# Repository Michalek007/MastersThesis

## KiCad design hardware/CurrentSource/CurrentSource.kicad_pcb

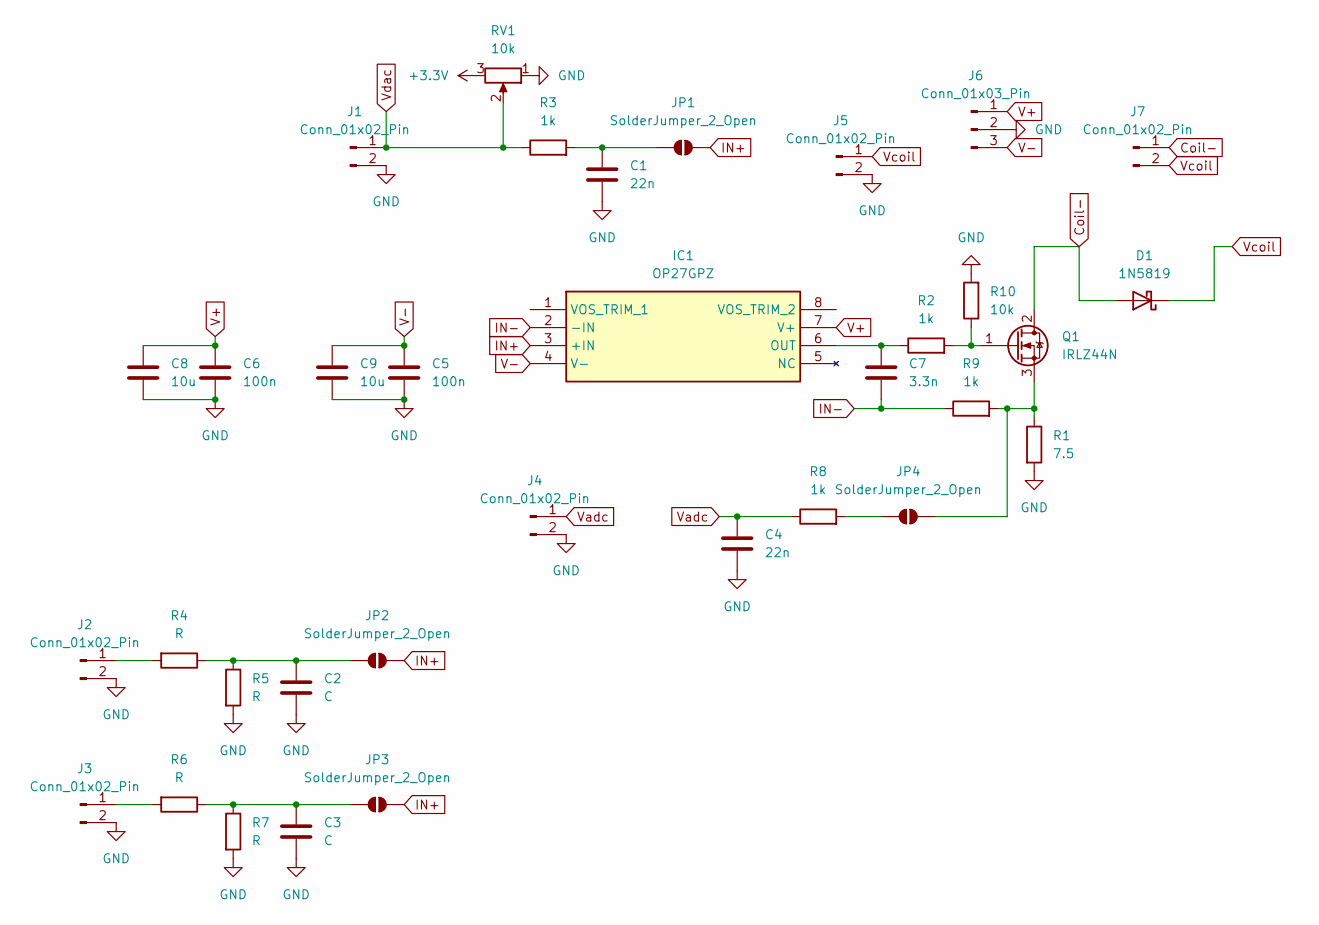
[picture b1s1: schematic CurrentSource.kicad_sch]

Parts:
C1, C4: 22n; C_0805_2012Metric
C2, C3: C; C_0805_2012Metric
C5, C6: 100n; C_0805_2012Metric
C7: 3.3n; C_0805_2012Metric
C8, C9: 10u; C_0805_2012Metric
D1: 1N5819; D_DO-41_SOD81_P10.16mm_Horizontal
IC1: OP27GPZ; DIP794W56P254L959H533Q8N; Mouser Part Number 584-OP27GPZ
J1, J2, J3, J4, J5, J7: Conn_01x02_Pin; PinHeader_1x02_P2.54mm_Vertical
J6: Conn_01x03_Pin; PinHeader_1x03_P2.54mm_Vertical
JP1, JP2, JP3, JP4: SolderJumper_2_Open; SolderJumper-2_P1.3mm_Open_Pad1.0x1.5mm
Q1: IRLZ44N; TO-220-3_Vertical
R1: 7.5; TO-220-2_Vertical
R2, R3, R8, R9: 1k; R_0805_2012Metric
R4, R5, R6, R7: R; R_0805_2012Metric
R10: 10k; R_0805_2012Metric
RV1: 10k; Potentiometer_ACP_CA6-H2,5_Horizontal

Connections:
+3.3V: RV1.3
Coil-: D1.2 (A), J7.1, Q1.2 (D)
GND: C1.2, C2.2, C3.2, C4.2, C5.2, C6.2, C8.2, C9.2, J1.2, J2.2, J3.2, J4.2, J5.2, J6.2, R1.2, R5.2, R7.2, R10.2, RV1.1
IN+: IC1.3 (+IN), JP1.2 (B), JP2.2 (B), JP3.2 (B)
IN-: C7.1, IC1.2 (-IN), R9.1
unnamed: C7.2, IC1.6 (OUT), R2.1
unnamed: J2.1, R4.2
unnamed: J3.1, R6.2
unnamed: C1.1, JP1.1 (A), R3.2
unnamed: C2.1, JP2.1 (A), R4.1, R5.1
unnamed: C3.1, JP3.1 (A), R6.1, R7.1
unnamed: JP4.1 (A), R8.2
unnamed: JP4.2 (B), Q1.3 (S), R1.1, R9.2
unnamed: Q1.1 (G), R2.2, R10.1
V+: C6.1, C8.1, IC1.7 (V+), J6.1
V-: C5.1, C9.1, IC1.4 (V-), J6.3
Vadc: C4.1, J4.1, R8.1
Vcoil: D1.1 (K), J5.1, J7.2
Vdac: J1.1, R3.1, RV1.2

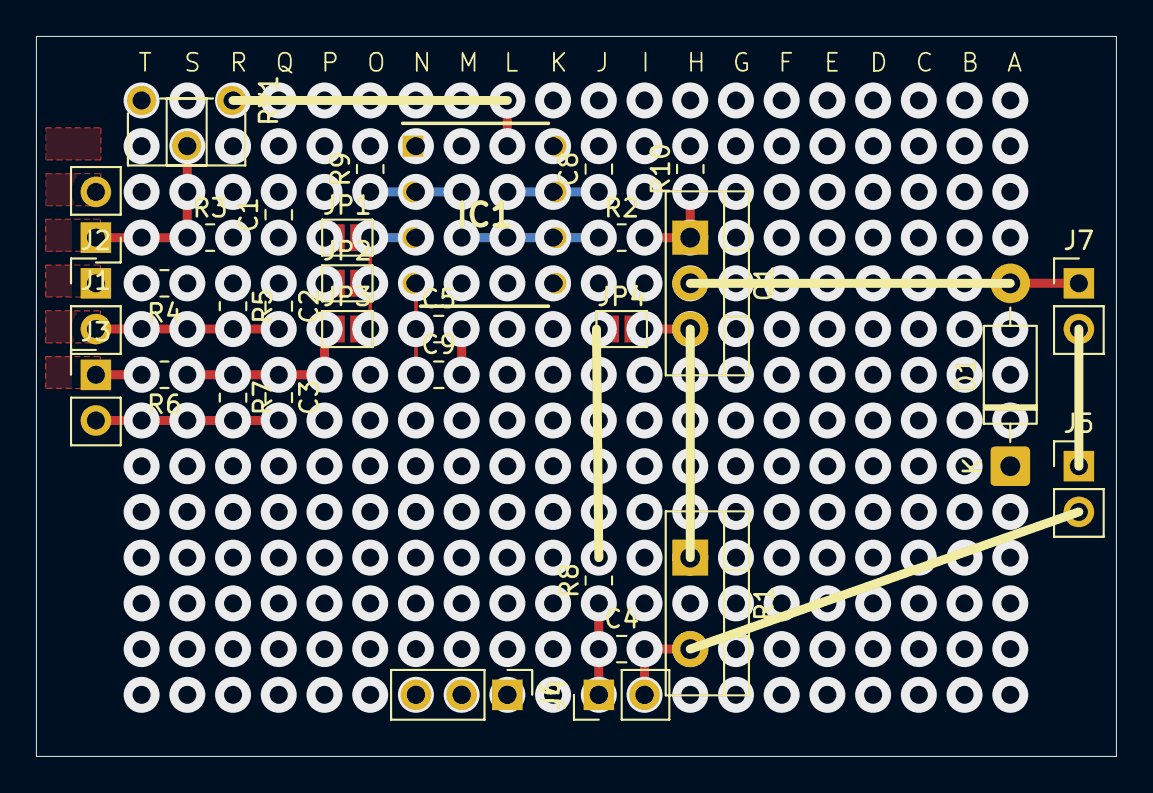
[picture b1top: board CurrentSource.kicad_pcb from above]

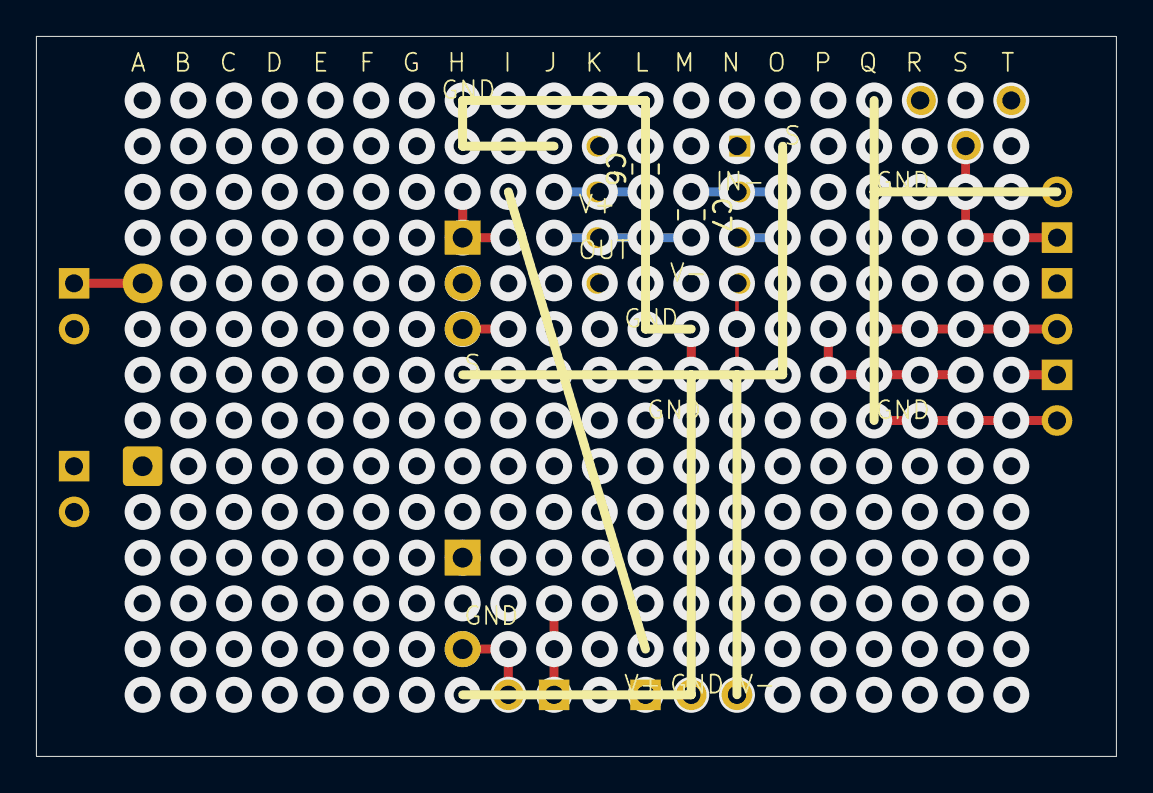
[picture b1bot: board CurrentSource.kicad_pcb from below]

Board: 2 copper layers, 60.0 x 40.0 mm, 34 parts (2 on the bottom side), 18 nets.

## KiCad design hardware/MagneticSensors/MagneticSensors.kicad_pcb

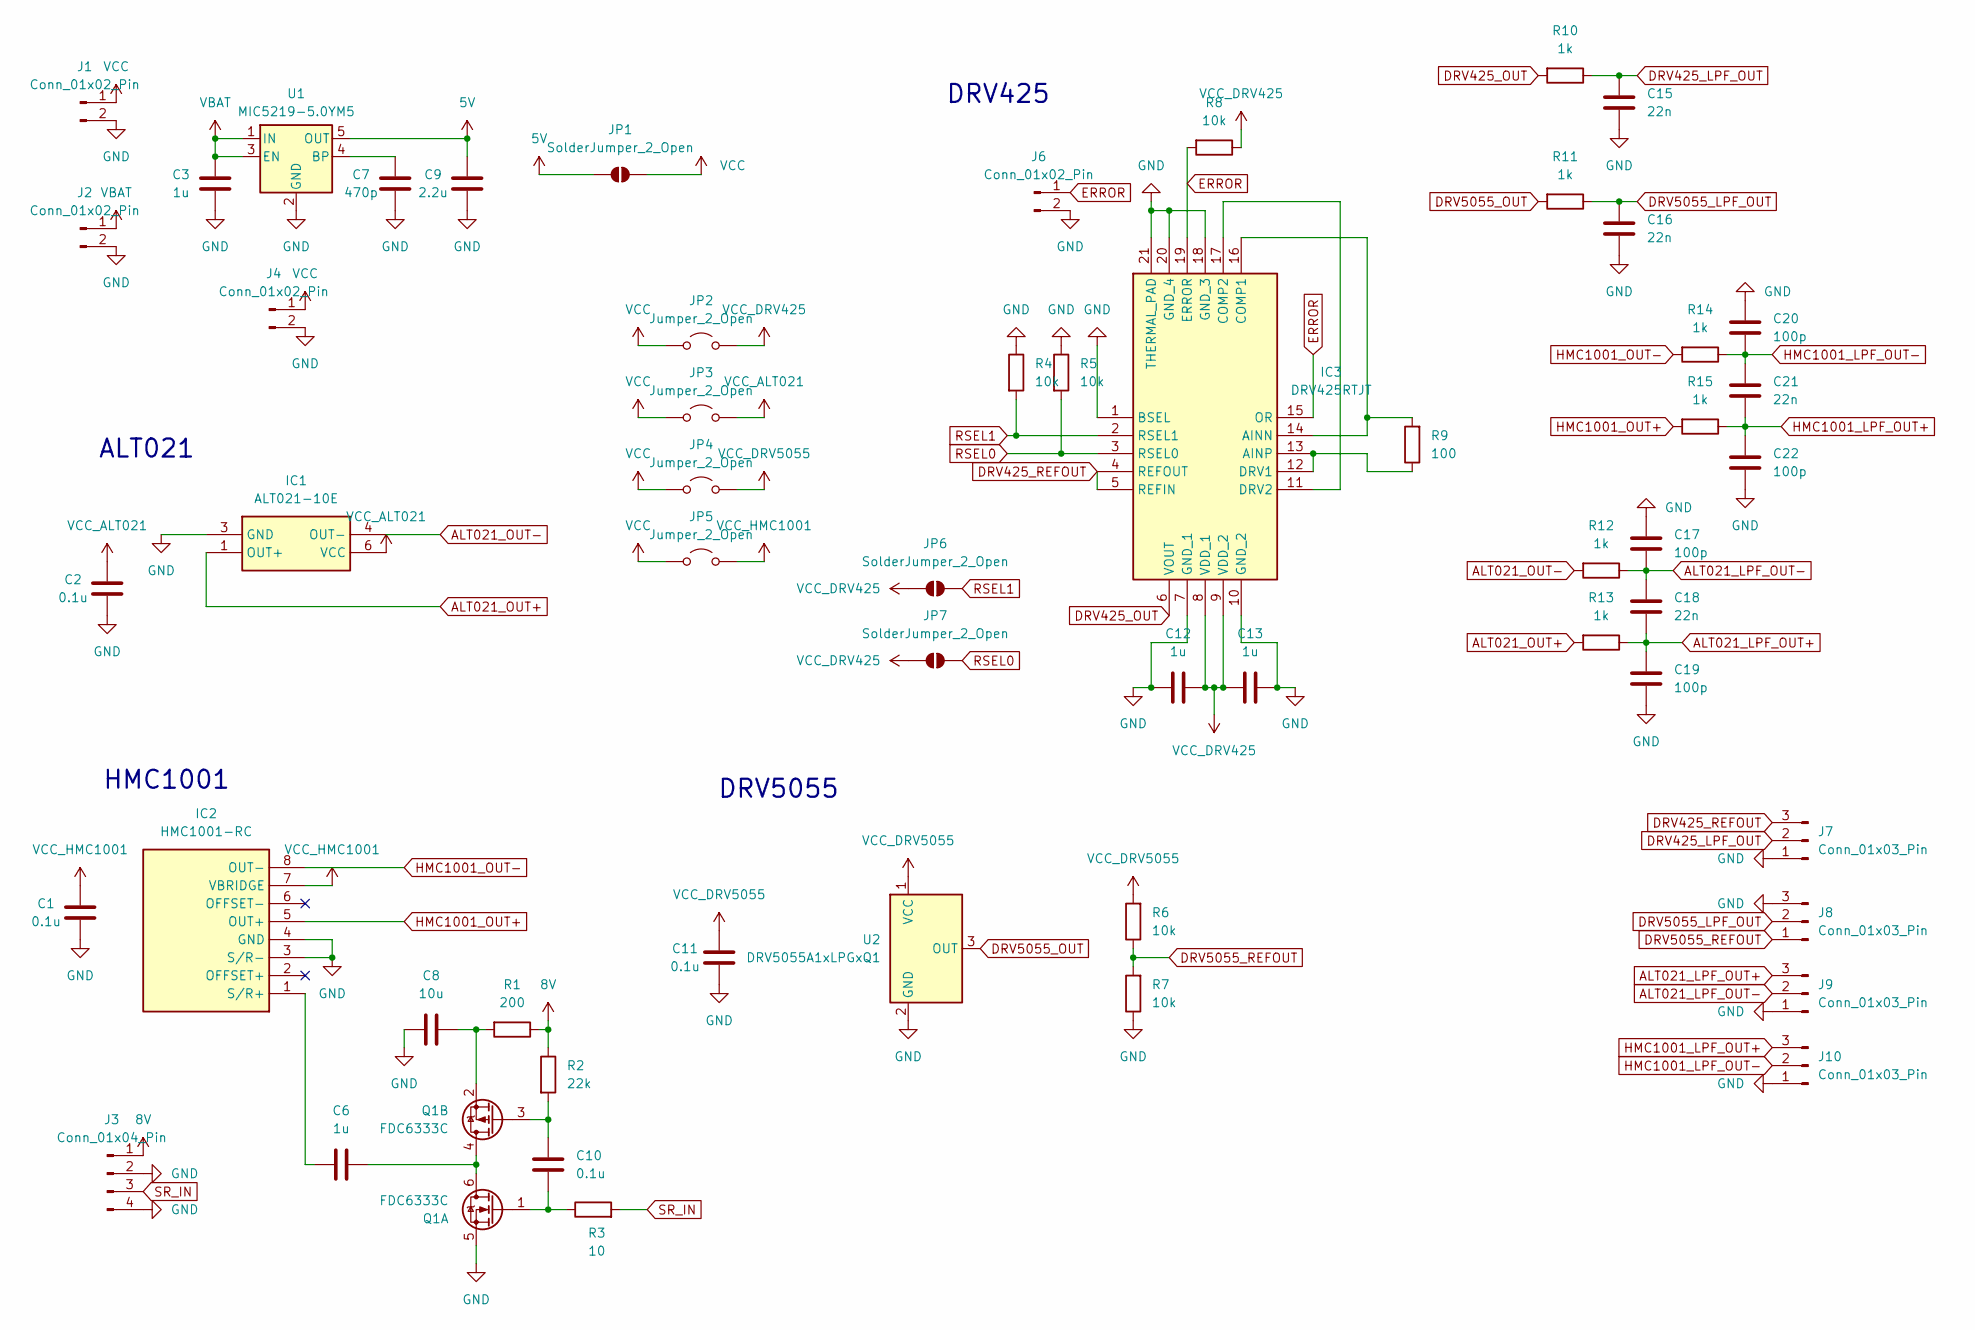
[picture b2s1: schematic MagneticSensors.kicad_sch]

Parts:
C1, C2, C10, C11: 0.1u; C_0805_2012Metric_Pad1.18x1.45mm_HandSolder
C3, C6, C12, C13: 1u; C_0805_2012Metric_Pad1.18x1.45mm_HandSolder
C7: 470p; C_0805_2012Metric_Pad1.18x1.45mm_HandSolder
C8: 10u; C_0805_2012Metric_Pad1.18x1.45mm_HandSolder
C9: 2.2u; C_0805_2012Metric_Pad1.18x1.45mm_HandSolder
C15, C16, C18, C21: 22n; C_0805_2012Metric_Pad1.18x1.45mm_HandSolder
C17, C19, C20, C22: 100p; C_0805_2012Metric_Pad1.18x1.45mm_HandSolder
IC1: ALT021-10E; 2.5x2.5DFN6
IC2: HMC1001-RC; HMC1001RC; Mouser Part Number 785-HMC1001-RC
IC3: DRV425RTJT; QFN50P400X400X80-21N-D; Mouser Part Number 595-DRV425RTJT
J1, J2, J4, J6: Conn_01x02_Pin; PinHeader_1x02_P2.54mm_Vertical
J3: Conn_01x04_Pin; PinHeader_1x04_P2.54mm_Vertical
J7, J8, J9, J10: Conn_01x03_Pin; PinHeader_1x03_P2.54mm_Vertical
JP1, JP6, JP7: SolderJumper_2_Open; SolderJumper-2_P1.3mm_Open_Pad1.0x1.5mm
JP2, JP3, JP4, JP5: Jumper_2_Open; PinHeader_1x02_P2.54mm_Vertical
Q1: FDC6333C; SOT95P275X110-6N
R1: 200; R_0805_2012Metric_Pad1.20x1.40mm_HandSolder
R2: 22k; R_0805_2012Metric_Pad1.20x1.40mm_HandSolder
R3: 10; R_0805_2012Metric_Pad1.20x1.40mm_HandSolder
R4, R5, R6, R7, R8: 10k; R_0805_2012Metric_Pad1.20x1.40mm_HandSolder
R9: 100; R_0805_2012Metric_Pad1.20x1.40mm_HandSolder
R10, R11, R12, R13, R14, R15: 1k; R_0805_2012Metric_Pad1.20x1.40mm_HandSolder
U1: MIC5219-5.0YM5; SOT-23-5
U2: DRV5055A1xLPGxQ1; TO-92_Inline

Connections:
5V: C9.2, JP1.1 (A), U1.5 (OUT)
8V: J3.1, R1.1, R2.1
ALT021_LPF_OUT+: C18.2, C19.1, J9.3, R13.1
ALT021_LPF_OUT-: C17.2, C18.1, J9.2, R12.1
ALT021_OUT+: IC1.1 (OUT+), R13.2
ALT021_OUT-: IC1.4 (OUT-), R12.2
DRV425_LPF_OUT: C15.1, J7.2, R10.1
DRV425_OUT: IC3.6 (VOUT), R10.2
DRV425_REFOUT: IC3.4 (REFOUT), IC3.5 (REFIN), J7.3
DRV5055_LPF_OUT: C16.1, J8.2, R11.1
DRV5055_OUT: R11.2, U2.3 (OUT)
DRV5055_REFOUT: J8.1, R6.1, R7.2
ERROR: IC3.15 (OR), IC3.19 (ERROR), J6.1, R8.2
GND: C1.1, C2.1, C3.1, C7.1, C8.2, C9.1, C11.1, C12.2, C13.2, C15.2, C16.2, C17.1, C19.2, C20.1, C22.2, IC1.3 (GND), IC2.3 (S/R-), IC2.4 (GND), IC3.1 (BSEL), IC3.7 (GND_1), IC3.10 (GND_2), IC3.18 (GND_3), IC3.20 (GND_4), IC3.21 (THERMAL_PAD), J1.2, J2.2, J3.2, J3.4, J4.2, J6.2, J7.1, J8.3, J9.1, J10.1, Q1.5 (S1), R4.1, R5.1, R7.1, U1.2 (GND), U2.2 (GND)
HMC1001_LPF_OUT+: C21.2, C22.1, J10.3, R15.1
HMC1001_LPF_OUT-: C20.2, C21.1, J10.2, R14.1
HMC1001_OUT+: IC2.5 (OUT+), R15.2
HMC1001_OUT-: IC2.8 (OUT-), R14.2
unnamed: C6.2, IC2.1 (S/R+)
unnamed: IC3.14 (AINN), IC3.16 (COMP1), R9.2
unnamed: IC3.12 (DRV1), IC3.13 (AINP), R9.1
unnamed: IC3.11 (DRV2), IC3.17 (COMP2)
unnamed: C6.1, Q1.4 (D2), Q1.6 (D1)
unnamed: C10.2, Q1.1 (G1), R3.1
unnamed: C10.1, Q1.3 (G2), R2.2
unnamed: C8.1, Q1.2 (S2), R1.2
unnamed: C7.2, U1.4 (BP)
RSEL0: IC3.3 (RSEL0), JP7.2 (B), R5.2
RSEL1: IC3.2 (RSEL1), JP6.2 (B), R4.2
SR_IN: J3.3, R3.2
VBAT: C3.2, J2.1, U1.1 (IN), U1.3 (EN)
VCC: J1.1, J4.1, JP1.2 (B), JP2.1 (A), JP3.1 (A), JP4.1 (A), JP5.1 (A)
VCC_ALT021: C2.2, IC1.6 (VCC), JP3.2 (B)
VCC_DRV425: C12.1, C13.1, IC3.8 (VDD_1), IC3.9 (VDD_2), JP2.2 (B), JP6.1 (A), JP7.1 (A), R8.1
VCC_DRV5055: C11.2, JP4.2 (B), R6.2, U2.1 (VCC)
VCC_HMC1001: C1.2, IC2.7 (VBRIDGE), JP5.2 (B)

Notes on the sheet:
DRV425
ALT021
DRV5055
HMC1001

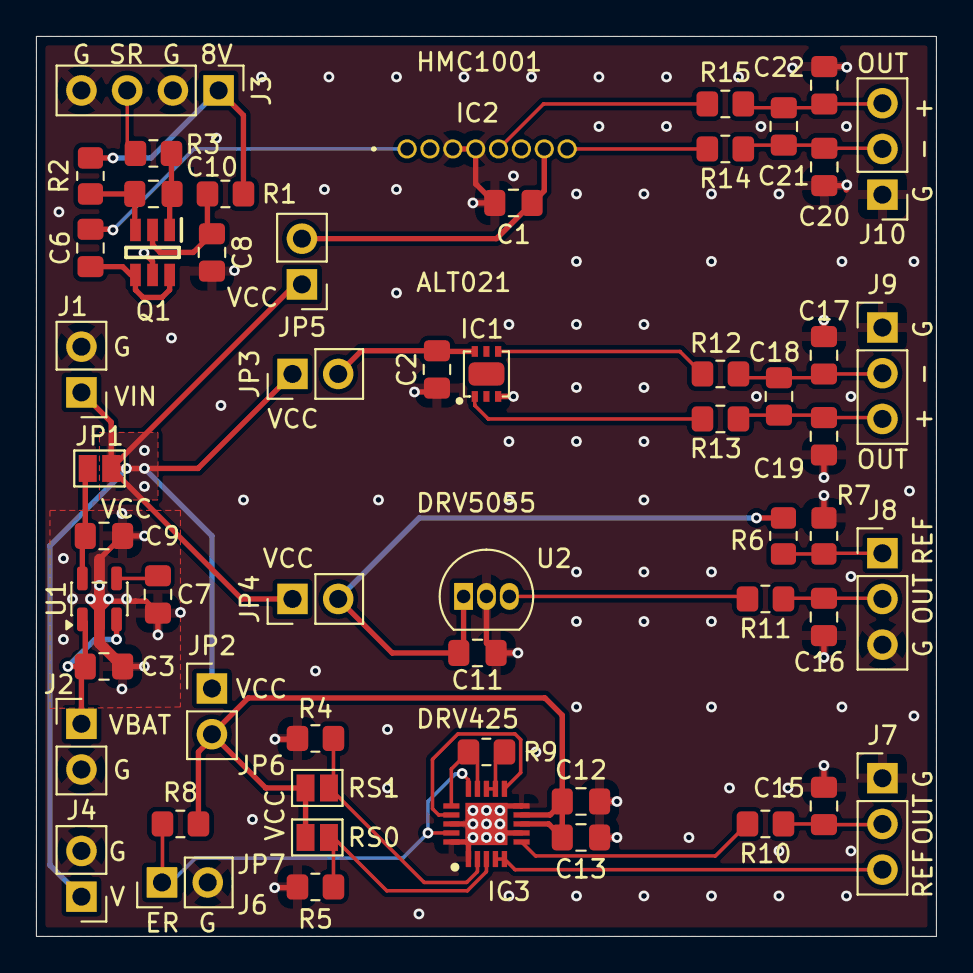
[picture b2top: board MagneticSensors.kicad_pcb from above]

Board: 4 copper layers, 50.0 x 50.0 mm, 56 parts (0 on the bottom side), 36 nets.

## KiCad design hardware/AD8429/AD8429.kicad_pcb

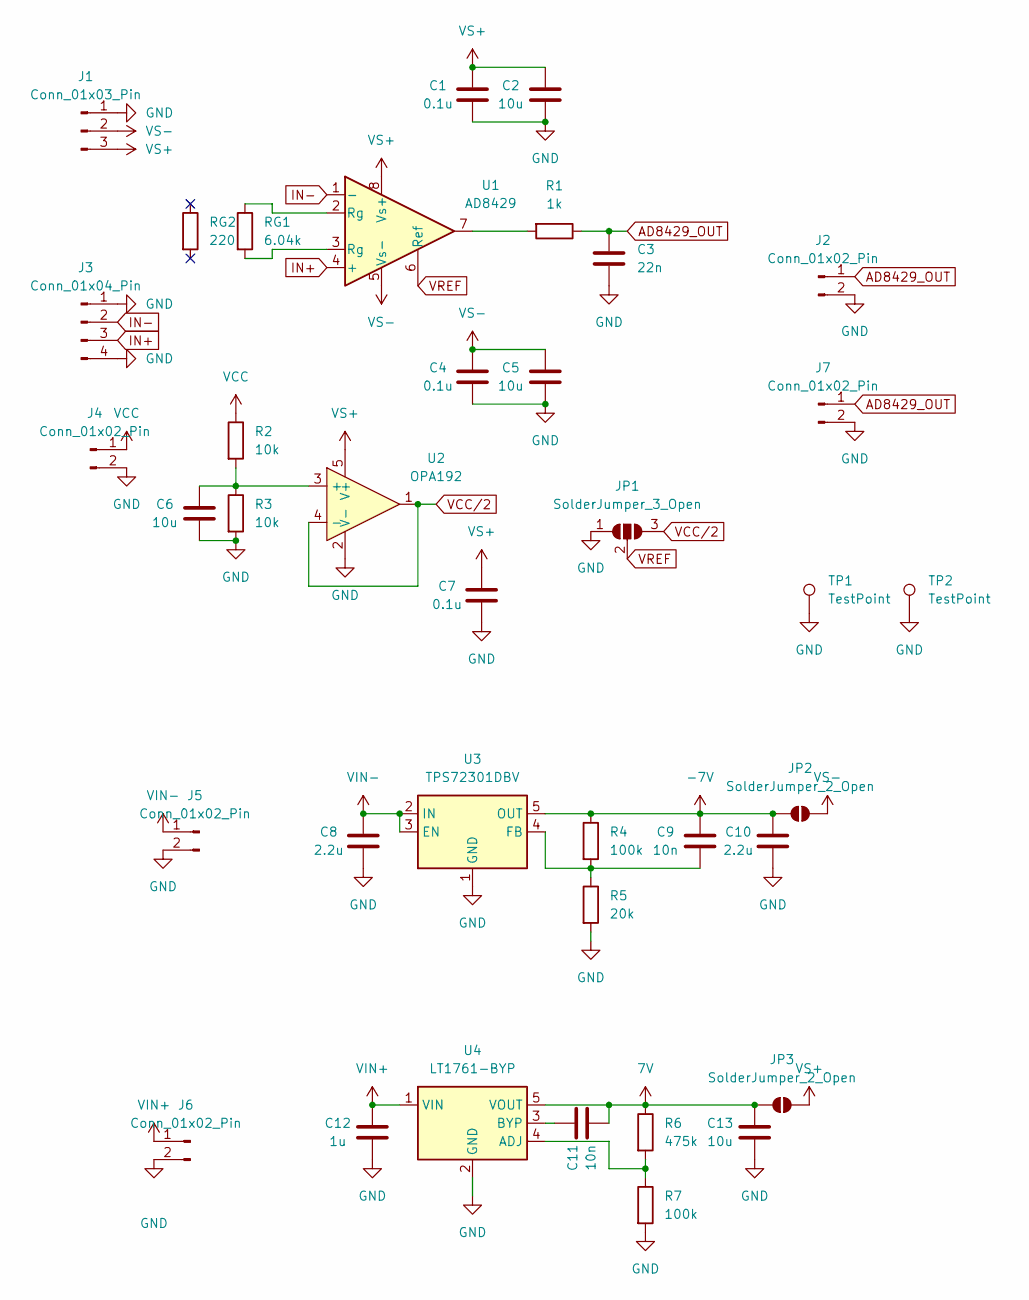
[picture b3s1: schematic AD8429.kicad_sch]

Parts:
C1, C4, C7: 0.1u; C_0805_2012Metric_Pad1.18x1.45mm_HandSolder
C2, C5, C6, C13: 10u; C_0805_2012Metric_Pad1.18x1.45mm_HandSolder
C3: 22n; C_0805_2012Metric_Pad1.18x1.45mm_HandSolder
C8, C10: 2.2u; C_0805_2012Metric_Pad1.18x1.45mm_HandSolder
C9, C11: 10n; C_0805_2012Metric_Pad1.18x1.45mm_HandSolder
C12: 1u; C_0805_2012Metric_Pad1.18x1.45mm_HandSolder
J1: Conn_01x03_Pin; PinHeader_1x03_P2.54mm_Vertical
J2, J4, J5, J6, J7: Conn_01x02_Pin; PinHeader_1x02_P2.54mm_Vertical
J3: Conn_01x04_Pin; PinHeader_1x04_P2.54mm_Vertical
JP1: SolderJumper_3_Open; SolderJumper-3_P1.3mm_Open_Pad1.0x1.5mm
JP2, JP3: SolderJumper_2_Open; SolderJumper-2_P1.3mm_Open_Pad1.0x1.5mm
R1: 1k; R_0805_2012Metric_Pad1.20x1.40mm_HandSolder
R2, R3: 10k; R_0805_2012Metric_Pad1.20x1.40mm_HandSolder
R4, R7: 100k; R_0805_2012Metric_Pad1.20x1.40mm_HandSolder
R5: 20k; R_0805_2012Metric_Pad1.20x1.40mm_HandSolder
R6: 475k; R_0805_2012Metric_Pad1.20x1.40mm_HandSolder
RG1: 6.04k; R_0805_2012Metric_Pad1.20x1.40mm_HandSolder
RG2: 220; R_0805_2012Metric_Pad1.20x1.40mm_HandSolder
TP1, TP2: TestPoint; TestPoint_Keystone_5000-5004_Miniature
U1: AD8429; SOIC127P600X175-8N
U2: OPA192; SOT95P280X145-5N
U3: TPS72301DBV; SOT-23-5
U4: LT1761-BYP; TSOT-23-5

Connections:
7V: C11.1, C13.2, JP3.1 (A), R6.1, U4.5 (VOUT)
-7V: C9.2, C10.2, JP2.1 (A), R4.1, U3.5 (OUT)
AD8429_OUT: C3.1, J2.1, J7.1, R1.1
GND: C1.1, C2.1, C3.2, C4.1, C5.1, C6.1, C7.1, C8.1, C10.1, C12.1, C13.1, J1.1, J2.2, J3.1, J3.4, J4.2, J5.2, J6.2, J7.2, JP1.1 (A), R3.2, R5.2, R7.2, TP1.1, TP2.1, U2.2 (V-), U3.1 (GND), U4.2 (GND)
IN+: J3.3, U1.4 (+)
IN-: J3.2, U1.1 (-)
unnamed: R1.2, U1.7
unnamed: RG1.1, U1.2 (Rg)
unnamed: RG1.2, U1.3 (Rg)
unnamed: C6.2, R2.2, R3.1, U2.3 (+)
unnamed: C9.1, R4.2, R5.1, U3.4 (FB)
unnamed: R6.2, R7.1, U4.4 (ADJ)
unnamed: C11.2, U4.3 (BYP)
VCC: J4.1, R2.1
VCC/2: JP1.3 (B), U2.1, U2.4 (-)
VIN+: C12.2, J6.1, U4.1 (VIN)
VIN-: C8.2, J5.1, U3.2 (IN), U3.3 (EN)
VREF: JP1.2 (C), U1.6 (Ref)
VS+: C1.2, C2.2, C7.2, J1.3, JP3.2 (B), U1.8 (Vs+), U2.5 (V+)
VS-: C4.2, C5.2, J1.2, JP2.2 (B), U1.5 (Vs-)

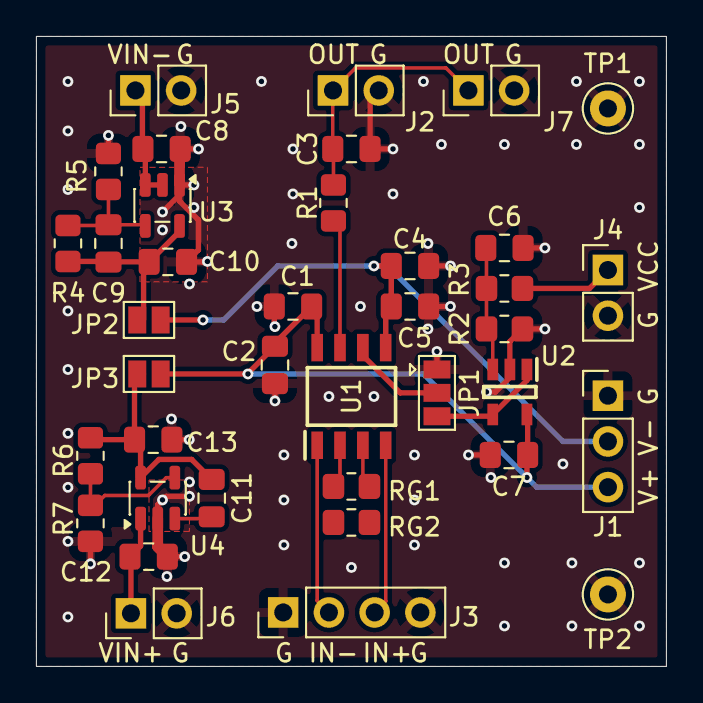
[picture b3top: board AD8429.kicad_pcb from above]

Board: 4 copper layers, 35.0 x 35.0 mm, 38 parts (0 on the bottom side), 20 nets.
